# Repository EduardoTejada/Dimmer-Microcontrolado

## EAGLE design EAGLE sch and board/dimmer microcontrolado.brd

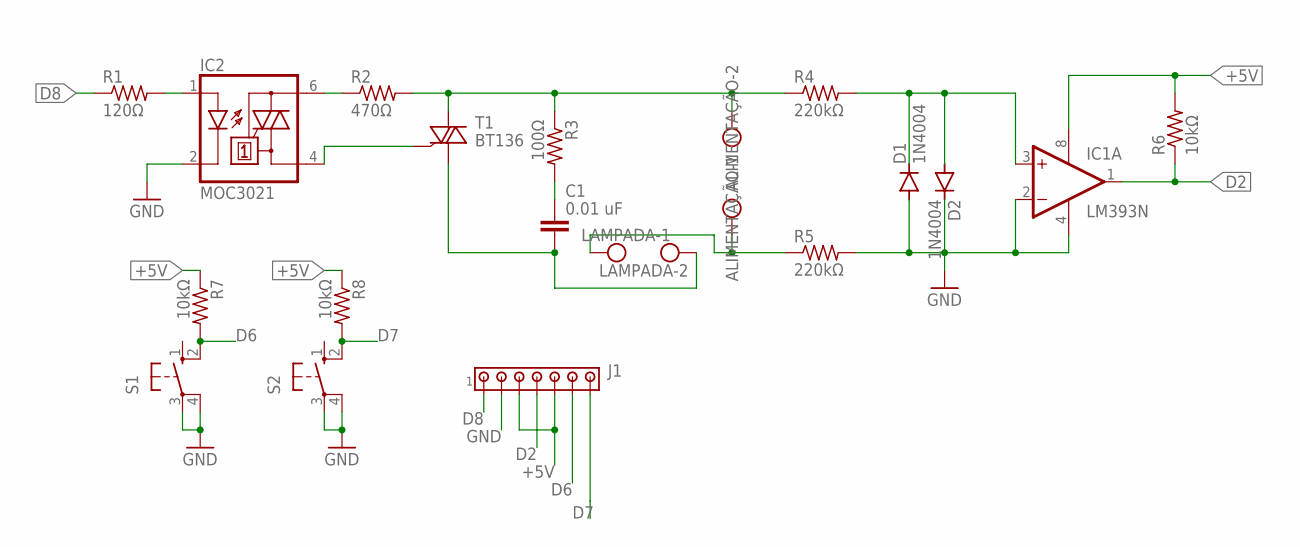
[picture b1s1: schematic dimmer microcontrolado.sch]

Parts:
ALIMENTAÇÃO: AK300/2
C1: 0.01 uF; C075-032X103
D1, D2: 1N4004; DO35-7
IC1: LM393N; DIL08
IC2: MOC3021; DIL06
J1: MTA07-100; 10X07MTA
LAMPADA: AK300/2
R1: 120Ω; 0207/10
R2: 470Ω; 0207/10
R3: 100Ω; 0207/10
R4, R5: 220kΩ; 0207/10
R6, R7, R8: 10kΩ; 0207/10
S1, S2: 10-XX; B3F-10XX
T1: BT136; TO220AB

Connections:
+5V: IC1.8 (V+), J1.3, J1.5, R6.2, R7.1, R8.1
D2: IC1.1 (OUT), J1.4, R6.1
D6: J1.6, R7.2, S1.2 (S1)
D7: J1.7, R8.2, S2.2 (S1)
D8: J1.1, R1.1
GND: D1.A, D2.C, IC1.2 (-IN), IC1.4 (V-), IC2.2 (C), J1.2, R5.2, S1.3, S1.4 (P1), S2.3, S2.4 (P1)
unnamed: IC2.1 (A), R1.2
unnamed: IC2.6 (A2), R2.1
unnamed: C1.1, R3.2
unnamed: IC2.4 (A1), T1.3 (G)
unnamed: ALIMENTAÇÃO.1, R2.2, R3.1, R4.1, T1.2 (A2)
unnamed: C1.2, LAMPADA.2, T1.1 (A1)
unnamed: ALIMENTAÇÃO.2, LAMPADA.1, R5.1
unnamed: D1.C, D2.A, IC1.3 (+IN), R4.2

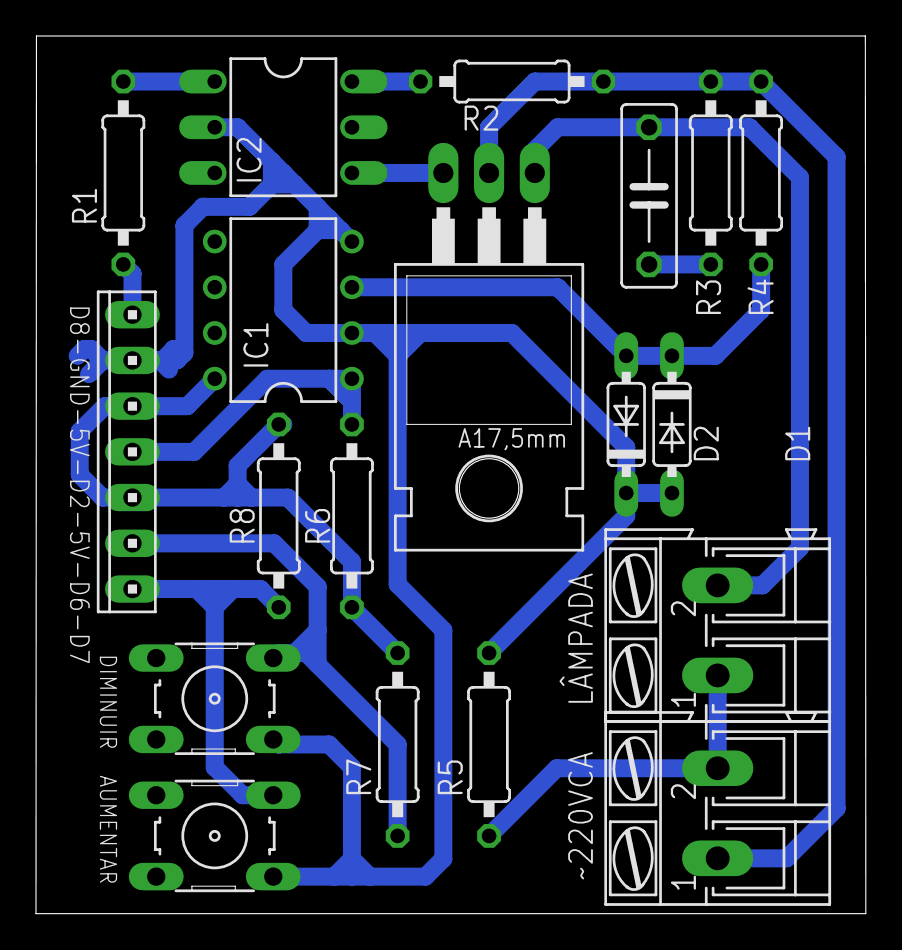
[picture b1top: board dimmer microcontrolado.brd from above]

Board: 2 copper layers, 46.1 x 48.8 mm, 19 parts (0 on the bottom side), 14 nets.

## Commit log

2021-11-21 Main upload
2021-11-21 changed the board
    Testing changes in the board file
